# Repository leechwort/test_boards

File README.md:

# test_boards
Testing boards for different electronic components

Currently they included boards with:

* A4988
* audio board with TDA8551
* test board for OLED UG-2864ASYCG01 display

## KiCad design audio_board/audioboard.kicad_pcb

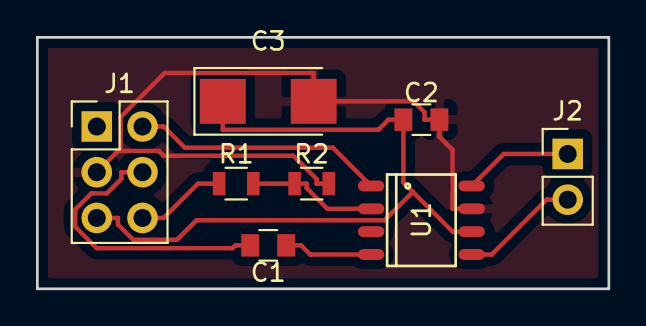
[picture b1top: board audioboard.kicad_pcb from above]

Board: 2 copper layers, 31.8 x 14.0 mm, 8 parts (0 on the bottom side), 9 nets.

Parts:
C1: 330nF; C_0805
C2: 100n; C_0805
C3: 220uF; CP_Tantalum_Case-C_EIA-6032-28_Reflow
J1: CONN_02X03; Pin_Header_Straight_2x03_Pitch2.54mm
J2: CONN_01X02; Pin_Header_Straight_1x02_Pitch2.54mm
R1, R2: 1k; R_0805
U1: TDA8551; SO-8

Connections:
+5V: C2.1, C3.1, J1.5, U1.6
GND: C2.2, C3.2, J1.3, R2.2, U1.7
unnamed: C1.1, U1.4
unnamed: C1.2, J1.4
unnamed: J1.2, U1.1
unnamed: J1.6, R1.1
unnamed: J2.1, U1.8
unnamed: J2.2, U1.5
unnamed: R1.2, R2.1, U1.2

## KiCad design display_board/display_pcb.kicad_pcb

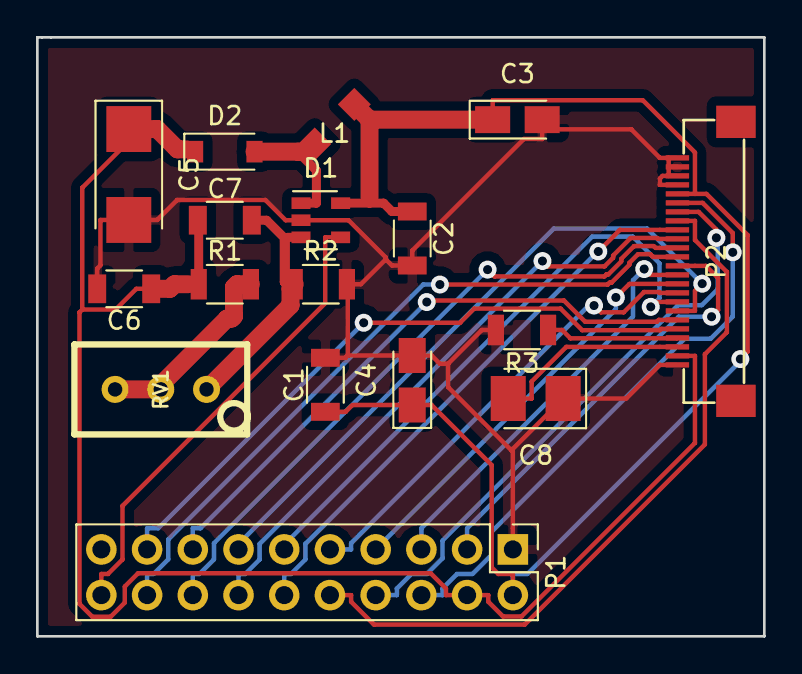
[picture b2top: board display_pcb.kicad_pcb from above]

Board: 2 copper layers, 40.4 x 33.3 mm, 17 parts (0 on the bottom side), 24 nets.

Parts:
C1, C6: 0.1 uF; C_1206
C2: 100n; C_1206
C3, C4: 10 uF; CP_Tantalum_Case-A_EIA-3216-18_Reflow
C5: 10 uF; CP_Tantalum_Case-C_EIA-6032-28_Reflow
C7: 47 pF; C_1206
C8: 4.7uF; CP_Tantalum_Case-B_EIA-3528-21_Reflow
D1: TPS61040; SOT-23-5
D2: D_Schottky_Small; D_SOD-123
L1: 4.7 uH; CDRH2D18
P1: CONN_02X10; Pin_Header_Straight_2x10_Pitch2.54mm
P2: FFC24x0.5mm; ffc-24-0.5mm
R1: 300k; R_1206
R2: 120k; R_1206
R3: 910k; R_1206
RV1: 500k; BOURNS-3296W

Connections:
+3V3: C1.1, C2.1, C3.1, C4.1, D1.5, L1.1, P1.2, P2.20
BS1: P1.6, P2.19
BS2: P1.8, P2.18
CS: P1.10, P2.17
D0: P1.3, P2.12
D1: P1.5, P2.11
D2: P1.7, P2.10
D3: P1.9, P2.9
D4: P1.11, P2.8
D5: P1.13, P2.7
D6: P1.15, P2.6
D7: P1.17, P2.5
DC: P1.14, P2.15
EN: D1.4, P1.20
GND: C1.2, C2.2, C3.2, C4.2, C5.2, C6.2, C8.1, D1.2, P1.1, P2.1, P2.21, P2.22, P2.23, P2.24, R2.2, R3.2
unnamed: C7.2, D1.3, R2.1, RV1.3
unnamed: C8.2, P2.3
unnamed: D1.1, D2.2, L1.2
unnamed: P2.4, R3.1
unnamed: R1.2, RV1.1, RV1.2
RD: P1.18, P2.13
RES: P1.12, P2.16
RW: P1.16, P2.14
VCC: C5.1, C6.1, C7.1, D2.1, P1.4, P2.2, R1.1

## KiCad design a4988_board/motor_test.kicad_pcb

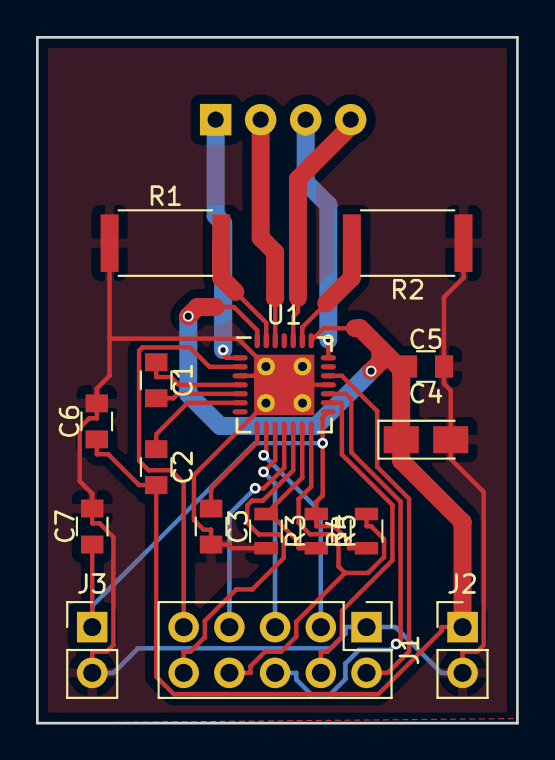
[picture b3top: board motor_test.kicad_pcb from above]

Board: 2 copper layers, 26.7 x 38.1 mm, 17 parts (1 on the bottom side), 23 nets.

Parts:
C1, C2: 100n; C_0805
C3, C5, C6, C7: 220n; C_0805
C4: CP1_Small; CP_Tantalum_Case-A_EIA-3216-18_Reflow
J1: CONN_02X05; Pin_Header_Straight_2x05_Pitch2.54mm
J2, J3: CONN_01X02; Pin_Header_Straight_1x02_Pitch2.54mm
J4: CONN_01X04_MALE; JST_XH_B04B-XH-A_04x2.50mm_Straight
R1, R2: 0.05; R_2512
R3: 10k; R_0805
R4: 100k; R_0805
R5: NP; R_0805
U1: A4988; QFN-28-1EP_5x5mm_Pitch0.5mm

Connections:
DIR: J1.2, U1.19
ENABLE: J1.9, U1.2
GND: C3.2, C4.2, C5.2, C6.2, C7.2, J1.1, J2.2, J3.2, R1.1, R2.1, R3.2, U1.3, U1.18, U1.29
MS1: J1.3, U1.9
MS2: J1.5, U1.10
MS3: J1.7, U1.11
unnamed: C1.1, U1.4
unnamed: C1.2, U1.5
unnamed: C2.1, U1.6
unnamed: C3.1, U1.8
unnamed: R1.2, U1.27
unnamed: R2.2, U1.23
unnamed: R3.1, R5.2, U1.13
OUT1A: J4.4, U1.24
OUT1B: J4.3, U1.21
OUT2A: J4.2, U1.26
OUT2B: J4.1, U1.1
REF: J1.6, U1.17
RESET: J1.10, U1.12
SLEEP: J1.8, R4.2, U1.14
STEP: J1.4, U1.16
VDD: C7.1, J3.1, R4.1, R5.1, U1.15
VDDA: C2.2, C4.1, C5.1, C6.1, J2.1, U1.22, U1.28

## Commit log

2017-03-27 Added files
2017-03-27 Added README
2017-03-27 Fixed markdown
